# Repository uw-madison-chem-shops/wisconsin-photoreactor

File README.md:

# Wisconsin Photoreactor Platform (WPP)

An open source photoreactor platform. 3D printed enclosure, commercially available components, and a little bit of custom circuitry.

The WPP has been published in Organic Letters.
Please read our article to learn more about the motivation behind the WPP and to see examples of photochemistry being driven using this reactor.

>[Versatile Open-Source Photoreactor Architecture for Photocatalysis Across the Visible Spectrum](https://doi.org/10.1021/acs.orglett.1c01910); Philip P. Lampkin, Blaise J. Thompson, and Samuel H. Gellman; Org. Lett. 2021, 23, 13, 5277–5281

## Repository

This is an open source hardware project licensed under the CERN Open Hardware License Version 2 - Permissive.
Please see the LICENSE file for the complete license.

This repository is being mirrored to several version control systems in an attempt to ensure maximum availability.

| name             | url                                                                             |
| ---------------- | ------------------------------------------------------------------------------- |
| blaise           | https://git.blaise.zone/uw-madison-chem-shops/wisconsin-photoreactor.git/about/ | 
| Codeburg         | https://codeberg.org/uw-madison-chem-shops/wisconsin-photoreactor               |
| GitHub (primary) | https://github.com/uw-madison-chem-shops/wisconsin-photoreactor                 |
| GitLab           | https://gitlab.com/uw-madison-chem-shops/wisconsin-photoreactor                 |

## Safety

The Wisconsin Photoreactor Platform is for use by trained chemists.

WPP apparatuses utilize high-intensity light emitting diodes (LED) that can cause eye damage if proper safety precautions are not observed. 
A light-blocking shield should be utilized whenever operating a WPP apparatus.
Care must be taken to ensure the light-blocking shield employed adequately blocks light emitted by a WPP photon source from directly reaching a user.
Use of light-filtering safety glasses alongside a light-blocking shield can provide additional protection.

## Fabrication and Operation Instructions

This repository contains detailed instructions for fabrication, operation and documentation of WPP devices.
Please see [wpp-fabrication-operation.pdf](./fabrication-and-operation-instructions/wpp-fabrication-operation.pdf)

A video guide covering part sourcing, 3D-printing, electronics manufacturing, assembly and use of Wisconsin photoreactors is available on [youtube](http://www.youtube.com/watch?v=fkLr17i4FgE)

## Enclosure

The WPP is designed around a mechanically robust and simple 3D printed enclosure.

Every WPP device has the same base, see directory `photoreactor-base`.
WPP reaction modules are meant to be switched based on the reaction vessel used.
See directory `photoreactor-reaction-modules` for our growing collection of reaction modules for common vessel types.
For safe WPP device operation, a light blocking shield is recommended. 
See directory `photoreactor-light-shield`, for a 3D-printable light-blocking cover for WPP devices.

## Electronics

The WPP incorporates small custom circuit boards providing control over reaction conditions.
Please see the fabrication instructions for more detailed information.

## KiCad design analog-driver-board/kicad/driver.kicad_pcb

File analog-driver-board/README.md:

# Analog Driver Board

A simple photoreactor driver board providing control over light intensity. This control is achieved through adjustment of the board-mounted potentiometer. No software is required, and multiple WPP reactors fitted with this board can be connected in series to a single power source. However, fan speed isn’t adjustable and is maintained at maximum.

Relative light intensity can be determined using the analog driver board test points and a multimeter. See operation instructions for more information.

The analog driver board is the recommended driver solution for a typical user.

## PCB

This PCB was designed using KiCAD version 5.
Refer to `driver.pdf` for schematic.
PCB images generated with [tracespace](https://github.com/tracespace/tracespace) follow.

## Bill of Materials

| reference      | value         | manufacturer | part number       | price | vendors |
| :------------- | :------------ | :----------- | :---------------- | :---- | :------ |
| C2             | 10u           | Yageo        | CC1206KKX7R8BB106 | $0.25 | [DigiKey](https://www.digikey.com/en/products/detail/yageo/CC1206KKX7R8BB106/5195365?s=N4IgTCBcDaIMJwIxgAwDYDSGAaB2ASgBwBCxi6IAugL5A) [Mouser](https://www.mouser.com/ProductDetail/Yageo/CC1206KKX7R8BB106/?qs=%2Fha2pyFadujG%252BB25mNGWlTAfaj3wXYmzjlPMfFLRNq4azOfH13S4tw%3D%3D) |
| D1             | (red)         | Lite-On      | LTST-C230KRKT     | $0.25 | [DigiKey](https://www.digikey.com/en/products/detail/lite-on-inc/LTST-C230KRKT/386857?s=N4IgTCBcDaIDIBUDKCC0BhMBmADAaQCU8EQBdAXyA) [Mouser](https://www.mouser.com/ProductDetail/Lite-On/LTST-C230KRKT/?qs=%2Fha2pyFadujtt9TjjkxDnLsTSvKz5QHldTfy80PY7mPtEP7ka44l7w%3D%3D) |
| J3, J4         | Barrel Jack   | CUI          | PJ-002A           | $1.50 | [DigiKey](https://www.digikey.com/en/products/detail/cui-devices/PJ-002A/96962) [Mouser](https://www.mouser.com/ProductDetail/CUI-Devices/PJ-002A/?qs=WyjlAZoYn51CKfAix9Mngw%3D%3D) |
| J5             | fan connector | Sullins      | PREC040SAAN-RC    | $0.50 | [DigiKey](https://www.digikey.com/en/products/detail/sullins-connector-solutions/PREC040SAAN-RC/2774814) |
| J7             | LED connector | Molex        | 0901471102        | $0.75 | [DigiKey](https://www.digikey.com/en/products/detail/molex/0901471102/3303846) |
| R1             | 6.8k          | Yageo        | RC1206FR-076K8L   | $0.10 | [DigiKey](https://www.digikey.com/en/products/detail/yageo/RC1206FR-076K8L/729028) |
| R2             | 100           | Yageo        | RC1206FR-07100RL  | $0.10 | [DigiKey](https://www.digikey.com/en/products/detail/yageo/RC1206FR-07100RL/728491?s=N4IgTCBcDaIAQCUDCBGMAGAbAMQQWnQHYV10EAZEAXQF8g) |
| R5             | 1k            | Yageo        | RC1206FR-071KL    | $0.10 | [DigiKey](https://www.digikey.com/en/products/detail/yageo/RC1206FR-071KL/728387?s=N4IgTCBcDaIEoGECMYAMA2AYnAtKg7EgNIAyIAugL5A) |
| RV1            | 2.2k          | Bourns       | 3362P-1-202TLF    | $3.00 | [DigiKey](https://www.digikey.com/en/products/detail/bourns-inc/3362P-1-202TLF/1232538?s=N4IgTCBcDaIMxwGxgAoFoCMawAYwBUAZAMRAF0BfIA) [Newark](https://www.newark.com/bourns/3362p-1-202tlf/trimmer-potentiometer-2kohm-10/dp/33M2835) |
| TP1            | (yellow)      | Keystone     | 5014              | $0.50 | [DigiKey](https://www.digikey.com/en/products/detail/keystone-electronics/5014/255336) |
| TP2            | (red)         | Keystone     | 5010              | $0.50 | [DigiKey](https://www.digikey.com/en/products/detail/keystone-electronics/5010/255332) |
| TP3            | (black)       | Keystone     | 5011              | $0.50 | [DigiKey](https://www.digikey.com/en/products/detail/keystone-electronics/5011/255333) |        |
| U2             | LED driver    | Mean Well    | LDD-1000L (pin)  | $6.00 | [DigiKey](https://www.digikey.com/en/products/detail/mean-well-usa-inc/LDD-1000L/7704722) [Allied](https://www.alliedelec.com/product/mean-well/ldd-1000l/70345765/) [Mouser](https://www.mouser.com/ProductDetail/MEAN-WELL/LDD-1000L?qs=JK6Bpmia%2FmvDNI%252Ba1vDDrA%3D%3D) [Newark](https://www.newark.com/mean-well/ldd-1000l/dc-dc-converter-analog-pwm-30w/dp/14AJ2201) [LEDSupply](https://www.ledsupply.com/led-drivers/mean-well-ldd-l-series-cc-step-down-mode)|

All prices are extended estimates in USD.
In general, these are overestimates, so this should be an upper-estimate on cost.
Many of these components can be substituted, so take the above as suggestions.
Boards themselves can be printed for approximately $5 each.

## Changelog

### Unprinted

### Revision C

#### Changed
- Removed wisconsin crest logo

#### Revision B

#### Fixed
- Fixedsign of LED terminals on silkscreen
- Voltage divider adjusted: R1 to 6.8k R2 to 100 ohm
- Adjusted voltage divider silkscreen

### Revision A

#### Added
- Initial design

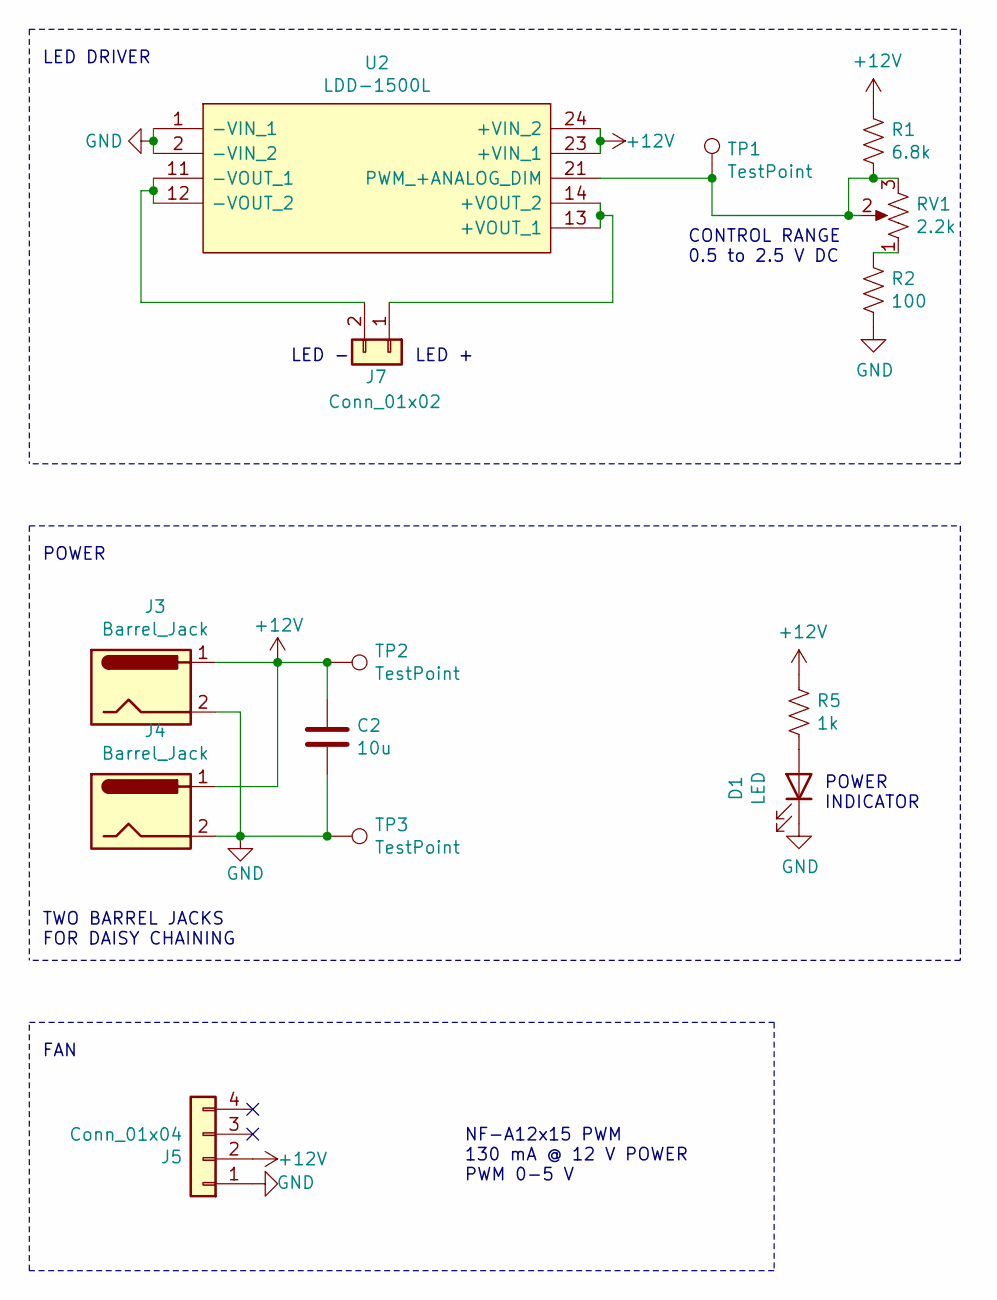
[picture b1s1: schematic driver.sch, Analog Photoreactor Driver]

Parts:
C2: 10u; C_1206_3216Metric_Pad1.33x1.80mm_HandSolder
D1: LED; LED_1206_3216Metric
J3, J4: Barrel_Jack; BarrelJack_Horizontal
J5: Conn_01x04; PinHeader_1x04_P2.54mm_Vertical
J7: Conn_01x02; PinSocket_1x02_P2.54mm_Vertical
R1: 6.8k; R_1206_3216Metric_Pad1.30x1.75mm_HandSolder
R2: 100; R_1206_3216Metric_Pad1.30x1.75mm_HandSolder
R5: 1k; R_1206_3216Metric_Pad1.30x1.75mm_HandSolder
RV1: 2.2k; TRIM_3362P-1-202TLF
TP1, TP2, TP3: TestPoint; TestPoint_THTPad_D3.0mm_Drill1.5mm
U2: LDD-1500L; LDD1500L; Manufacturer_Part_Number LDD-1500L; Mouser Part Number 709-LDD-1500L

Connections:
+12V: C2.2, J3.1, J4.1, J5.2, R1.1, R5.1, TP2.1, U2.23 (+VIN_1), U2.24 (+VIN_2)
GND: C2.1, D1.1 (K), J3.2, J4.2, J5.1, R2.2, TP3.1, U2.1 (-VIN_1), U2.2 (-VIN_2)
unnamed: D1.2 (A), R5.2
unnamed: J7.1, U2.13 (+VOUT_1), U2.14 (+VOUT_2)
unnamed: J7.2, U2.11 (-VOUT_1), U2.12 (-VOUT_2)
unnamed: R1.2, RV1.2, RV1.3, TP1.1, U2.21 (PWM_+ANALOG_DIM)
unnamed: R2.1, RV1.1

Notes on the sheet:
LED -
LED +
LED DRIVER
NF-A12x15 PWM 130 mA @ 12 V POWER PWM 0-5 V
FAN
TWO BARREL JACKS FOR DAISY CHAINING
POWER
POWER INDICATOR
CONTROL RANGE 0.5 to 2.5 V DC

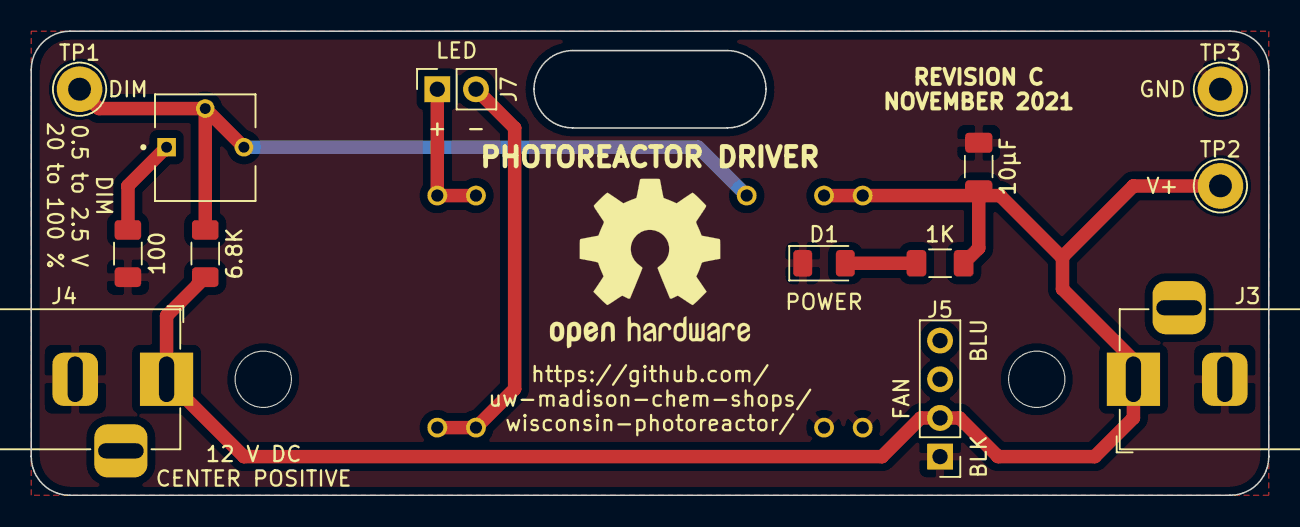
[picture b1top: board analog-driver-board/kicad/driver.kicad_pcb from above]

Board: 2 copper layers, 81.3 x 30.5 mm, 14 parts (1 on the bottom side), 7 nets.

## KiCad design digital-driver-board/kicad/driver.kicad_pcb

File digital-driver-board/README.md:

# digital-driver

A photoreactor driver board designed to be controlled digitally over I2C. For fabrication instructions, please see the fabrication and operation guide.

The digital driver is recommended for users who are experienced with electronics and interested in automating WPP devices.

## PCB

This PCB was designed using KiCAD version 5.
Refer to `driver.pdf` for schematic.
PCB images generated with [tracespace](https://github.com/tracespace/tracespace) follow.

Bill of Materials

| reference      | value         | manufacturer | part number          | price | vendors |
| :------------- | :------------ | :----------- | :------------------- | :---- | :------ |
|                | dip socket    | Mill-Max     | 110-93-308-61-001000 | $1.00 | [DigiKey](https://www.digikey.com/en/products/detail/mill-max-manufacturing-corp/110-93-308-61-001000/7734612) |
| C2             | 10u           | Yageo        | CC1206KKX7R8BB106    | $0.25 | [DigiKey](https://www.digikey.com/en/products/detail/yageo/CC1206KKX7R8BB106/5195365?s=N4IgTCBcDaIMJwIxgAwDYDSGAaB2ASgBwBCxi6IAugL5A) [Mouser](https://www.mouser.com/ProductDetail/Yageo/CC1206KKX7R8BB106/?qs=%2Fha2pyFadujG%252BB25mNGWlTAfaj3wXYmzjlPMfFLRNq4azOfH13S4tw%3D%3D) |
| C3             | 22u           | Yageo        | CC1206MKX7R7BB226    | $0.75 | [DigiKey](https://www.digikey.com/en/products/detail/yageo/cc1206mkx7r7bb226/7071713) |
| D1             | (red)         | Lite-On      | LTST-C230KRKT        | $0.25 | [DigiKey](https://www.digikey.com/en/products/detail/lite-on-inc/LTST-C230KRKT/386857?s=N4IgTCBcDaIDIBUDKCC0BhMBmADAaQCU8EQBdAXyA) [Mouser](https://www.mouser.com/ProductDetail/Lite-On/LTST-C230KRKT/?qs=%2Fha2pyFadujtt9TjjkxDnLsTSvKz5QHldTfy80PY7mPtEP7ka44l7w%3D%3D) |
| D2             | (blue)        | Lite-On      | LTST-C150TBKT        | $0.50 | [DigiKey](https://www.digikey.com/en/products/detail/lite-on-inc/LTST-C150TBKT/388526?s=N4IgTCBcDaIDIBUDKCC0BhAjAVgAwICEBpBEAXQF8g) |
| J1, J2         | i2c connector | JST          | S4B-PH-K-S(LF)(SN)   | $0.50 | [DigiKey](https://www.digikey.com/en/products/detail/jst-sales-america-inc/S4B-PH-K-S-LF-SN/926628) [Newark](https://www.newark.com/jst-japan-solderless-terminals/s4b-ph-k-s-lf-sn/connector-header-2mm-4-position/dp/38K8074) |
| J3, J4         | power input   | CUI          | PJ-002A              | $1.50 | [DigiKey](https://www.digikey.com/en/products/detail/cui-devices/PJ-002A/96962) [Mouser](https://www.mouser.com/ProductDetail/CUI-Devices/PJ-002A/?qs=WyjlAZoYn51CKfAix9Mngw%3D%3D) |
| J5             | fan connector | Sullins      | PREC040SAAN-RC       | $0.50 | [DigiKey](https://www.digikey.com/en/products/detail/sullins-connector-solutions/PREC040SAAN-RC/2774814) |
| J7             | LED connector | Molex        | 0901471102           | $0.75 | [DigiKey](https://www.digikey.com/en/products/detail/molex/0901471102/3303846) |
| PS1            | regulator     | CUI          | VXO7805-500-M-TR     | $3.00 | [DigiKey](https://www.digikey.com/en/products/detail/cui-inc/VXO7805-500-M-TR/11569188) [Newark](https://www.newark.com/cui/vxo7805-500-m-tr/non-isolated-dc-switching-regulator/dp/13AJ1536) |
| R1, R4, R6, R7 | 4.7k          | Yageo        | RC1206DR-074K7L      | $0.10 | [DigiKey](https://www.digikey.com/en/products/detail/yageo/rc1206dr-074k7l/5919134) |
| R2, R5         | 470           | Yageo        | RC1206FR-07470RL     | $0.10 | [DigiKey](https://www.digikey.com/en/products/detail/yageo/RC1206FR-07470RL/728934) |
| R3             | 10k           | Yageo        | RC1206FR-0710KL      | $0.10 | [DigiKey](https://www.digikey.com/en/products/detail/yageo/RC1206FR-0710KL/728483)  |
| U1             | microcontrol. | Microchip    | ATTINY85-20PU        | $1.50 | [DigiKey](https://www.digikey.com/en/products/detail/microchip-technology/attiny85-20pu/735469) [Newark](https://www.newark.com/microchip/attiny85-20pu/microcontroller-mcu-8-bit-attiny/dp/68T3808) |
| U2             | LED driver    | Mean Well    | LDD-1000L            | $6.00 | [DigiKey](https://www.digikey.com/en/products/detail/mean-well-usa-inc/LDD-1000L/7704722) [Allied](https://www.alliedelec.com/product/mean-well/ldd-1000l/70345765/) [Mouser](https://www.mouser.com/ProductDetail/MEAN-WELL/LDD-1000L?qs=JK6Bpmia%2FmvDNI%252Ba1vDDrA%3D%3D) [Newark](https://www.newark.com/mean-well/ldd-1000l/dc-dc-converter-analog-pwm-30w/dp/14AJ2201) [LEDSupply](https://www.ledsupply.com/led-drivers/mean-well-ldd-l-series-cc-step-down-mode)|

## I2C Interface

`<byte FAN SPEED>` `<byte LED INTENSITY>`

## Firmware

Find in "firmware" folder.

Use Arduino IDE.

We programmed the ATtiny85 using the sparkfun Tiny AVR Programmer: [PGM-11801](https://www.sparkfun.com/products/11801).

## Changelog

### Unprinted

#### Changed
- removed wisconsin crest logo

### Revision B

#### Fixed
- silk screen polarity markings for LED
- backwards I2C connectors

### Revision A

#### Added
- initial design

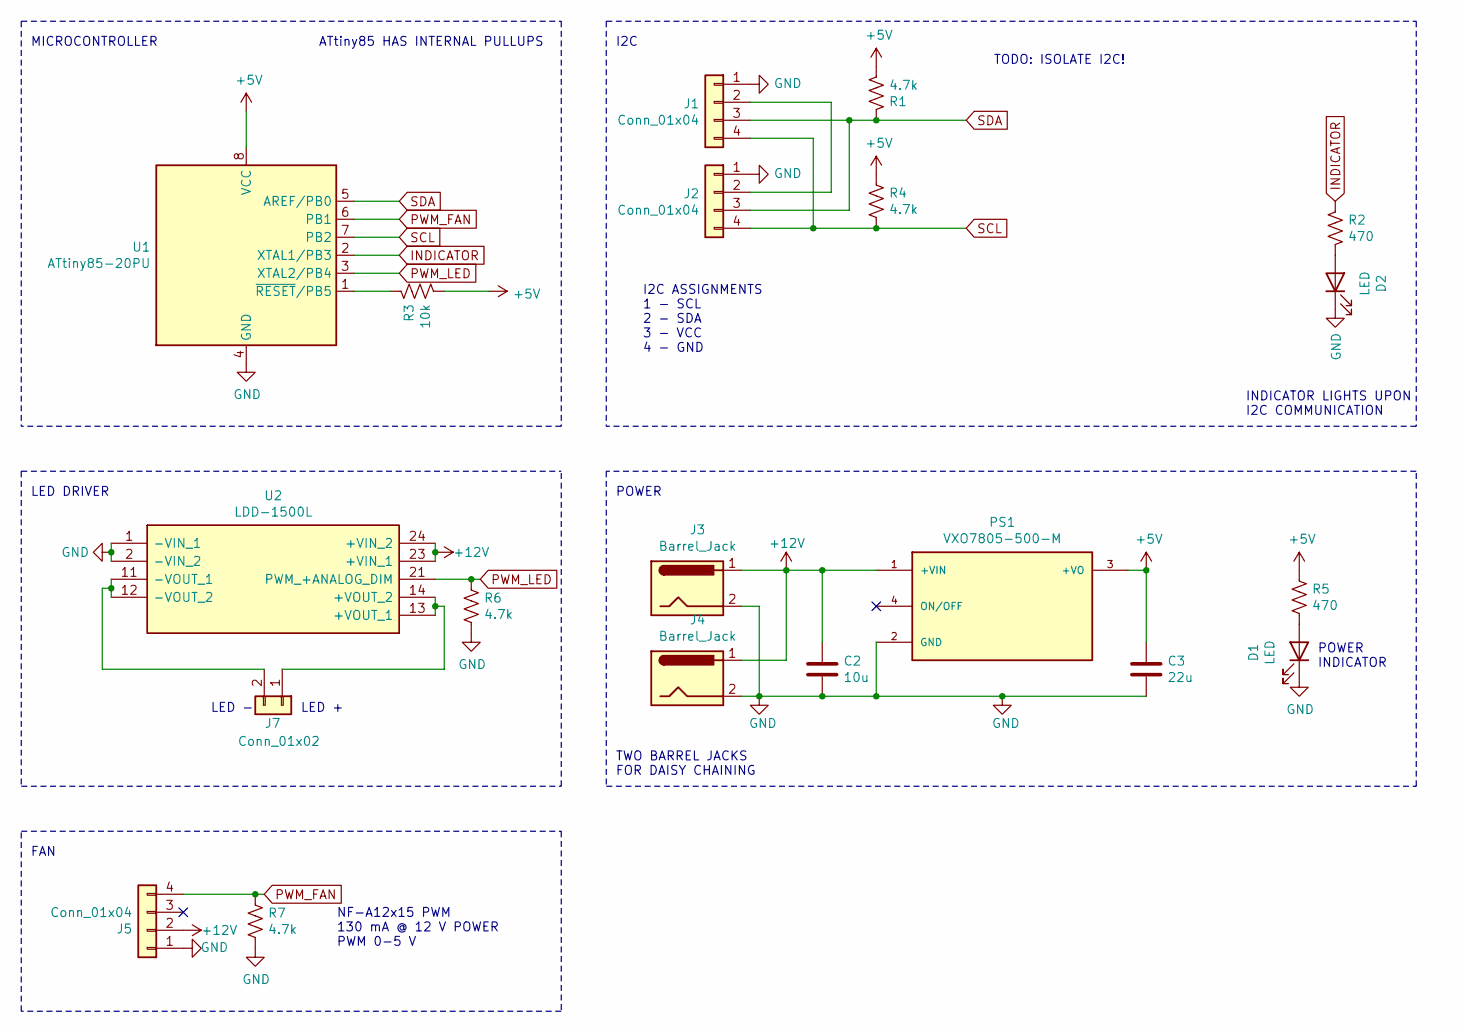
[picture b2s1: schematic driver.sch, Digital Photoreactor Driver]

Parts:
C2: 10u; C_1206_3216Metric_Pad1.33x1.80mm_HandSolder
C3: 22u; C_1206_3216Metric_Pad1.33x1.80mm_HandSolder
D1, D2: LED; LED_1206_3216Metric
J1, J2: Conn_01x04; JST_PH_S4B-PH-K_1x04_P2.00mm_Horizontal
J3, J4: Barrel_Jack; BarrelJack_Horizontal
J5: Conn_01x04; PinHeader_1x04_P2.54mm_Vertical
J7: Conn_01x02; PinSocket_1x02_P2.54mm_Vertical
PS1: VXO7805-500-M; CONV_VXO7805-500-M
R1, R4, R6, R7: 4.7k; R_1206_3216Metric_Pad1.30x1.75mm_HandSolder
R2, R5: 470; R_1206_3216Metric_Pad1.30x1.75mm_HandSolder
R3: 10k; R_1206_3216Metric_Pad1.30x1.75mm_HandSolder
U1: ATtiny85-20PU; DIP-8_W7.62mm_Socket
U2: LDD-1500L; LDD1500L; Manufacturer_Part_Number LDD-1500L; Mouser Part Number 709-LDD-1500L

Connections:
+5V: C3.1, PS1.3 (+VO), R1.2, R3.1, R4.1, R5.1, U1.8 (VCC)
+12V: C2.2, J3.1, J4.1, J5.2, PS1.1 (+VIN), U2.23 (+VIN_1), U2.24 (+VIN_2)
GND: C2.1, C3.2, D1.1 (K), D2.1 (K), J1.1, J2.1, J3.2, J4.2, J5.1, PS1.2 (GND), R6.2, R7.2, U1.4 (GND), U2.1 (-VIN_1), U2.2 (-VIN_2)
INDICATOR: R2.1, U1.2 (XTAL1/PB3)
unnamed: D1.2 (A), R5.2
unnamed: D2.2 (A), R2.2
unnamed: J1.2, J2.2
unnamed: J7.1, U2.13 (+VOUT_1), U2.14 (+VOUT_2)
unnamed: J7.2, U2.11 (-VOUT_1), U2.12 (-VOUT_2)
unnamed: R3.2, U1.1 (~RESET~/PB5)
PWM_FAN: J5.4, R7.1, U1.6 (PB1)
PWM_LED: R6.1, U1.3 (XTAL2/PB4), U2.21 (PWM_+ANALOG_DIM)
SCL: J1.4, J2.4, R4.2, U1.7 (PB2)
SDA: J1.3, J2.3, R1.1, U1.5 (AREF/PB0)

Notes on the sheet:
POWER
TWO BARREL JACKS FOR DAISY CHAINING
MICROCONTROLLER
ATtiny85 HAS INTERNAL PULLUPS
I2C ASSIGNMENTS 1 - SCL 2 - SDA 3 - VCC 4 - GND
POWER INDICATOR
LED -
LED +
LED DRIVER
FAN
INDICATOR LIGHTS UPON I2C COMMUNICATION
I2C
NF-A12x15 PWM 130 mA @ 12 V POWER PWM 0-5 V
TODO: ISOLATE I2C!

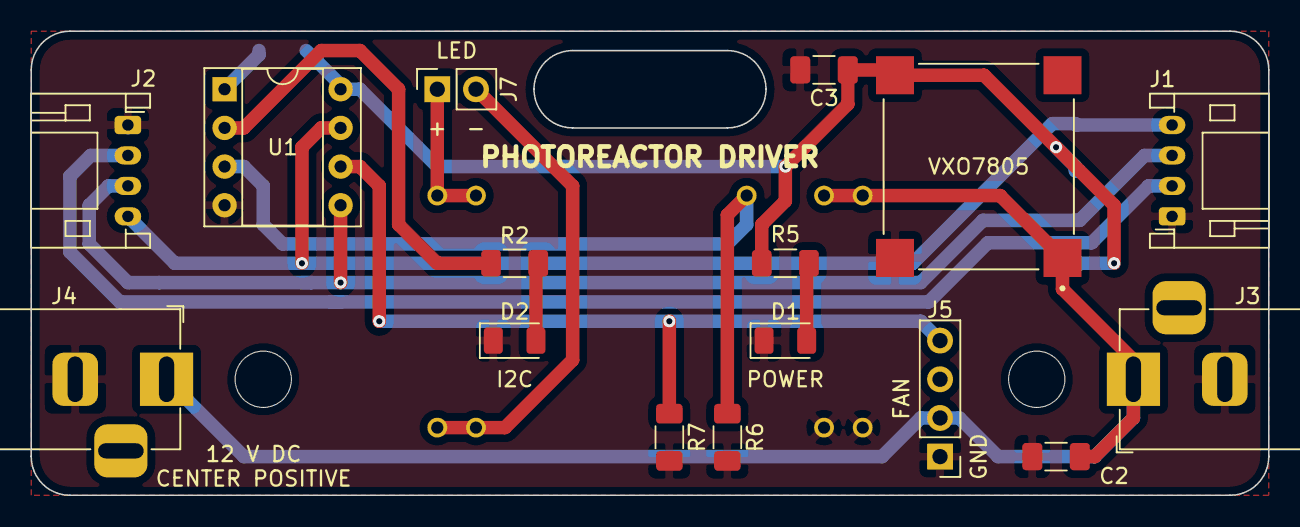
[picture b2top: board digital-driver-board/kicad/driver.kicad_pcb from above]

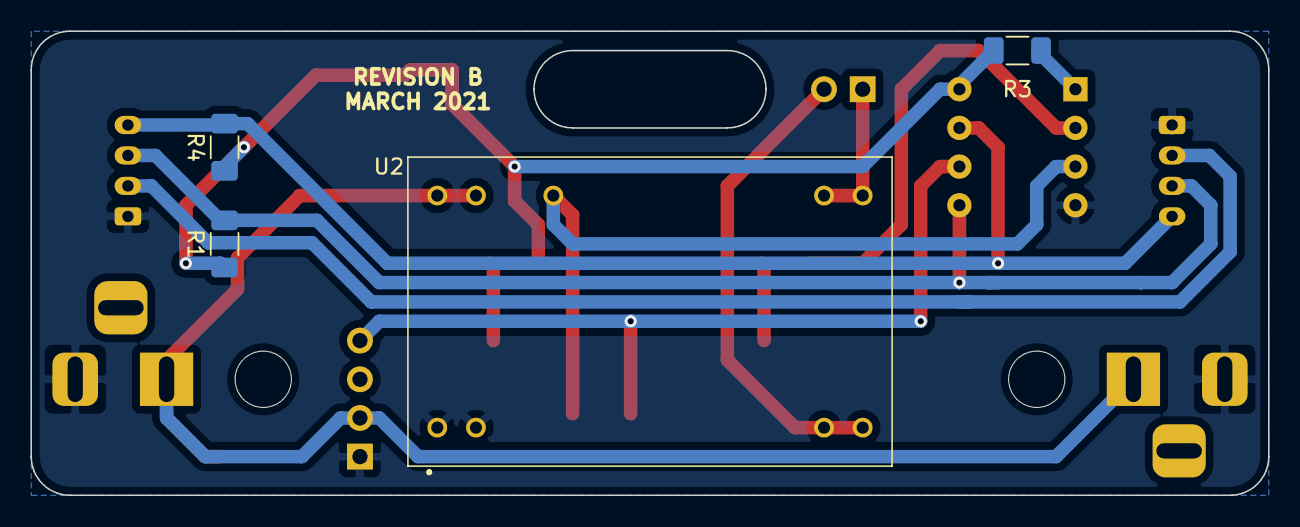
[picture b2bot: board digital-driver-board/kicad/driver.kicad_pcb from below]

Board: 2 copper layers, 81.3 x 30.5 mm, 20 parts (4 on the bottom side), 14 nets.

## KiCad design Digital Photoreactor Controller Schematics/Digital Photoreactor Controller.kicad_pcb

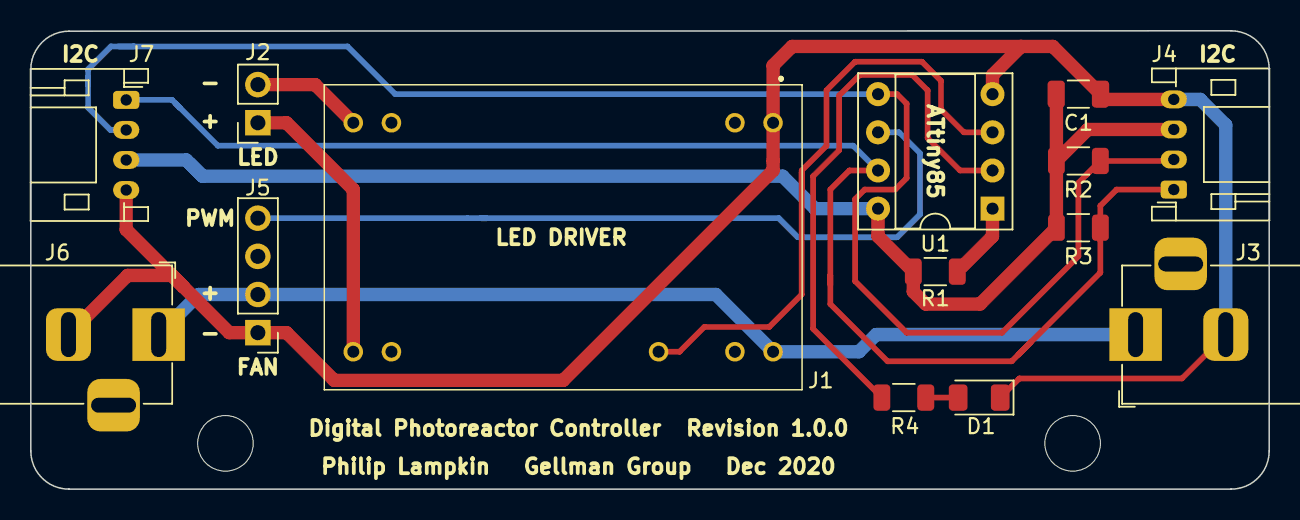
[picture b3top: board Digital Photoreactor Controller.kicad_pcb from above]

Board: 2 copper layers, 82.4 x 30.5 mm, 14 parts (0 on the bottom side), 12 nets.

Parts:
C1: 0.1uF; C_1206_3216Metric
D1: LED; LED_1206_3216Metric
J1: LDD-1500L; LDD1500L
J2: Conn_01x02; PinSocket_1x02_P2.54mm_Vertical
J3, J6: Barrel_Jack; BarrelJack_Horizontal
J4, J7: Conn_01x04; JST_PH_S4B-PH-K_1x04_P2.00mm_Horizontal
J5: Conn_01x04; PinHeader_1x04_P2.54mm_Vertical
R1: 10K; R_1206_3216Metric
R2, R3: 4.7K; R_1206_3216Metric
R4: 470; R_1206_3216Metric
U1: ATtiny85-20PU; DIP-8_W7.62mm_Socket

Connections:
+5V: C1.1, J4.3, J7.3, R1.1, R2.1, R3.1, U1.8
+12V: J1.24, J3.1, J5.2, J6.1
GND: C1.2, D1.1, J1.1, J3.2, J4.4, J5.1, J6.2, J7.4, U1.4
INDICATOR: R4.2, U1.2
unnamed: D1.2, R4.1
unnamed: J1.12, J2.2
unnamed: J1.13, J2.1
unnamed: R1.2, U1.1
PWM_FAN: J5.4, U1.6
PWM_LED: J1.21, U1.3
SCL: J4.1, J7.1, R3.2, U1.7
SDA: J4.2, J7.2, R2.2, U1.5

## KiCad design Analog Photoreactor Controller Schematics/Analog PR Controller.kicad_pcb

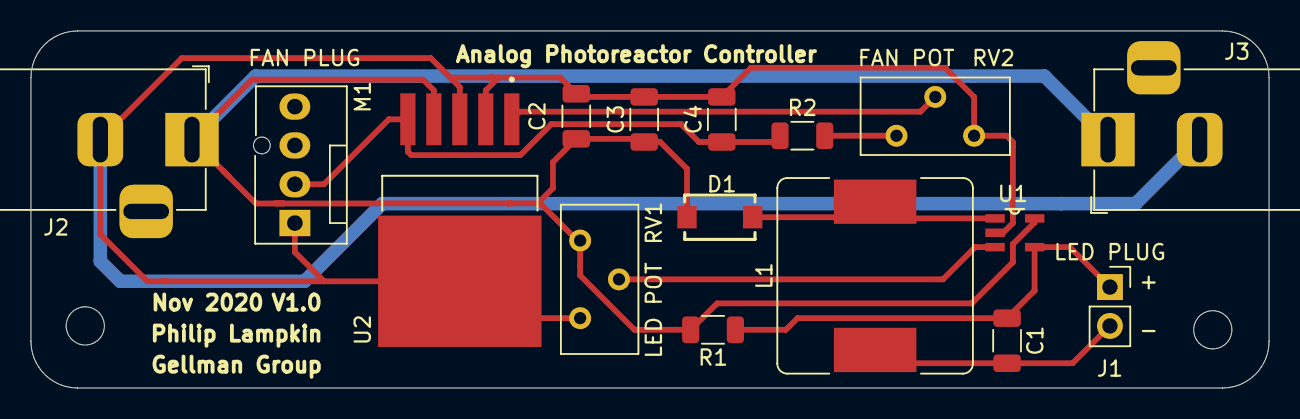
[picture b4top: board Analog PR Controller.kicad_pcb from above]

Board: 2 copper layers, 81.0 x 23.4 mm, 16 parts (0 on the bottom side), 9 nets.

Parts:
C1: 1uF; C_1206_3216Metric
C2: 2.2uF; C_1206_3216Metric
C3: 0.47uF; C_1206_3216Metric
C4: 22uF; C_1206_3216Metric
D1: MBRA140; SMA-DIODE
J1: Conn_01x02; PinSocket_1x02_P2.54mm_Vertical
J2, J3: Barrel_Jack; BarrelJack_Horizontal
L1: 33uH; L_Bourns_SRR1260
M1: Fan_4pin; FanPinHeader_1x04_P2.54mm_Vertical
R1: 0.3R; R_1206_3216Metric
R2: 8KOhm; R_1206_3216Metric
RV1: 100KOhm; Potentiometer_Bourns_3296Y_Vertical
RV2: 5kOhm1; Potentiometer_Bourns_3296Y_Vertical
U1: AL8805W5-7; SOT95P280X130-5N
U2: LM2941S; VREG_TPS79625KTTR

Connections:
+12V: C2.2, C3.1, D1.C, J2.1, J3.1, R1.2, RV1.1, U1.5, U2.4
GND: C2.1, C3.2, C4.2, J2.2, J3.2, M1.1, RV1.3, RV2.3, U1.2, U2.2, U2.3, U2.6
unnamed: C1.1, J1.1, R1.1, U1.4
unnamed: C1.2, J1.2, L1.1
unnamed: C4.1, M1.2, R2.1, U2.5
unnamed: D1.A, L1.2, U1.1
unnamed: R2.2, RV2.1
unnamed: RV1.2, U1.3
unnamed: RV2.2, U2.1

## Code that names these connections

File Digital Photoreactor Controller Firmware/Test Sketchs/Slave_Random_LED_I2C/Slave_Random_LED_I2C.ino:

////////////////////////////////////////////////////////////////////////////////////
// I2C test program for Digital Photoreactor Controller using TinyWireS library   //
//                    Run this slave program on the AtTiny85.                     //      
////////////////////////////////////////////////////////////////////////////////////
// This test program is adapted from the TinyWireS stress test program            //
// developed by Scott Hartog: https://github.com/rambo/TinyWire                   //
//                                                                                //
// The slave program receives via I2C N bytes of random data in a single          //
// receiveEvent() callback and stores that data in a global buffer.               //
// It then responds the first requestEvent() callback with the same data.         //
// The requestEvent() callback overwrites the data buffer with zeros after        //
// responding so it will only respond correctly to the first requestEvent()       //
// callback after each receiveEvent() callback. Subsequent requestEvent()         //
// will respond with 0xff for all data bytes.                                     //
//                                                                                //
//                                                                                //
// SETUP:                                                                         //
// AtTiny85 Pin 2 = PB3 = Blink LED                                               //
// Attiny85 Pin 3 (PB4) = LED PWM                                                 //
// AtTiny85 Pin 5 (PB0/SDA) = I2C SDA                                             //
//     connect to SDA on master with external pull-up (~4.7K)                     //
// AtTinyPin 6 (PB1) = Fan PWM                                                    //
// AtTiny Pin 7 (PB0/SCL) = I2C SCL                                               //
//     connect to SCL on master with external pull-up (~4.7K)                     //
// AtTiny Pin 1 (PB5/!RST)                                                        //
//     connect to reset on master (or just pull-up)                               //
//                                                                                //
////////////////////////////////////////////////////////////////////////////////////

#include "TinyWireS.h"                  // wrapper class for I2C slave routines

#define I2C_SLAVE_ADDR  0x26            // I2C slave address (38, 0x26), 

uint8_t master_data[16];               // global buffer to store data sent from the master.
uint8_t master_bytes;                  // global variable to number of bytes sent from the master.

const int LEDPin = 4;                  //Arduino pin 4, pin 3 on AtTiny85 pinout
const int FanPin = 1;                  //Arduino pin 1, pin 6 on AtTiny85 pinout
const int BlinkPin = 3;                //Arduino pin 3, pin 2 on AtTiny85 pinout

// Gets called when the ATtiny85 receives an I2C write slave request
void receiveEvent(uint8_t num_bytes)
{
  uint8_t i;
  
  // save the number of bytes sent from the master
  master_bytes = num_bytes;

  // store the data from the master into the data buffer
  for (i = 0; i < master_bytes; i++)
    master_data[i] = TinyWireS.receive();

  // set LED and Fan PWM duty to random byte values recieved from the master
  analogWrite(FanPin, master_data[0]);
  analogWrite(LEDPin, master_data[1]);

  // blink LED whenever data is successfuly recieved
  digitalWrite(BlinkPin, HIGH);
  delay(10);
  digitalWrite(BlinkPin, LOW);
  delay(10);

}

// Gets called when the ATtiny receives an i2c read slave request
void requestEvent()
{
  uint8_t i;
  
  // send the data buffer back to the master
  for (i = 0; i < master_bytes; i++)
    TinyWireS.send(master_data[i]);

  // corrupt the byte values in the data buffer
  // so that subsequent call won't match
  for (i = 0; i < master_bytes; i++)
    master_data[i] += 0x5a;

  // corrupt length of the request, but dont' make it zero
  
  // if the usiTwiSlave.c is working fine, then this number is completely irrelevant
  // because the requestEvent() callback will not be called again until
  // after the next receiveEvent() callback, so the master_data and
  // master_bytes variables will be set by that call.

  // If the usiTwiSlave.c has the issue of calling the requestFrom() callback
  // for each byte sent, the buffer will accumulate by this amount *for each byte
  // in the original request*.
  // 
  // Making it zero will obscure the 1-byte send issue in the usiTwiSlave.c
  // that is being tested.
  // Making it small will allow a few requests to succeed before the tx buffer
  // overflows and the usiTwiSlave.c hangs on the "while ( tmphead == txTail );"
  // line
  master_bytes = 2; 
}

void setup()
{
  // initialize the TinyWireS and usiTwiSlave libraries
  TinyWireS.begin(I2C_SLAVE_ADDR);      // init I2C Slave mode

  // register the onReceive() callback function
  TinyWireS.onReceive(receiveEvent);
  
  // register the onRequest() callback function
  TinyWireS.onRequest(requestEvent);

  pinMode(LEDPin, OUTPUT);   // set pin for LED PWM
  pinMode(FanPin, OUTPUT);   // set pin for Fan PWM
  pinMode(BlinkPin, OUTPUT); // set pin to blink LED
  
  TCCR0B = TCCR0B & 0b11111000 | 0b001; // sets internal timer of AtTiny85 to 31250 Hz for fast PWM for controlling fan speed
}

void loop()
{
  // this needs to be here 
  /////////////Does this really need to be here?????
  //TinyWireS_stop_check();
  // otherwise empty loop
}

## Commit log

2020-12-29 updated PCB w/ LED
2020-12-30 Commented and added blink LED function on receive data
2020-12-30 Commented and cleaned up code
2020-12-30 Wrote PR controller sketches for slave and master
2020-12-30 markdown readme
2020-12-30 Updated PCB routing
2020-12-30 Updated drill marks and edgecuts to be more uniform
2020-12-30 Added optimized lightsource bases in open and closed configuration
2021-01-06 Removed version numbers, removed open base, added final optimized closed base design
2021-01-19 restructure repository
2021-01-19 cleanup analog photoreactor
2021-01-19 cleanup documentation directory
2021-01-19 cleanup digital driver
2021-01-21 updated base to use heat insets, have compatability with zip tie anchors and better mounts for driver board
2021-01-25 digital driver prototype
2021-01-25 digital-driver readme
2021-01-25 digital-driver table newline
2021-01-25 tap-heatsink
2021-01-27 digital driver 1.0.0
2021-01-29 analog driver 1.0.0
2021-01-29 analog readme
2021-02-11 updated base designs
2021-03-05 analog-driver revision B
2021-03-05 parts list
2021-03-05 rearrange repository
2021-03-05 delete
2021-03-06 added enclosures for new vessel types, added WPR logo to base and cleaned up file names
2021-03-06 added LED emission spectra
2021-03-06 added README
2021-03-06 digital driver revision B
2021-03-06 emission spectra pictures
2021-03-06 rename
2021-03-06 duplicate removal
2021-03-12 updated amber spectrum
2021-03-25 coverart
2021-03-25 license
2021-03-25 organize analog-driver
2021-03-25 analog readme levels
2021-03-25 assembly instructions skeleton
2021-04-14 assembly skeleton
2021-04-14 new photos
2021-04-16 pcb assembly pictures
2021-04-16 led pictures
2021-04-19 first minimum viable assembly instructions
2021-04-19 populate readme
2021-04-24 added typical photon source emission spectra
2021-04-24 reworked LED emission spectra terminology
2021-04-24 updated LED terminology
2021-04-24 rename leds directory
2021-04-24 new coverart
2021-04-24 terminology update
2021-04-24 terminology updates
2021-04-24 added modules photo
2021-04-24 added base photo
2021-04-24 rough merge of content from operation instructions
2021-04-24 updated controller firmware with serial interface
2021-04-24 remove wisconsin crest logo
2021-04-25 Updated fabrication and operation guide up and including analog driver
2021-04-26 complete digital bom
2021-04-26 updated guide figures and text
2021-04-26 programming instructions
2021-04-26 added initial digital driver fabrication guide
2021-04-27 cleaned up digital driver board portion
2021-04-27 formatted documentation section
2021-04-27 polished entire guide
2021-04-27 Update README.md
    fixed spelling and updated wording.
2021-04-27 Update README.md
    updated wording and fixed spelling
2021-04-27 Update README.md
    Fixed wording and spelling
2021-04-27 Update README.md
    Fixed wording and spelling.
2021-04-27 Update README.md
    updated wording, fixed spelling.
2021-04-27 Update README.md
    Fixed wording.
2021-04-27 document fan, led connectors
2021-04-27 actually link to pdf
2021-04-27 added completed digital board figure
2021-04-27 updated guide with figure
2021-04-28 Edits from Sam
2021-04-28 Edits from Sam round 2
2021-05-18 Fixed photoreactor base naming, WPP branding and heat inset depth
2021-05-18 Updated README.md
    Added correct manufacturer part numbers
2021-05-18 updated 1mL to 2mL and item number
2021-05-18 Update README.md
    Added extra vendors for LDD-1000L driver
2021-05-18 Update README.md
    added LDD-1000L vendors
2021-05-18 updated fab guide 1mL to 2mL
2021-05-18 Update README.md
    added links to LED stars from LEDsupply
2021-05-19 fixed naming conventions
2021-05-19 removed Logos from all figures
2021-05-19 Cleaned up fabrication guide directory
2021-05-19 updated base graphic
2021-05-19 updated fab/op guide title page
2021-05-24 added light shield
2021-05-26 updated safety guide with light shield information
2021-05-26 added light shield photo to subdirectory
2021-05-26 updated operations guide title page
2021-05-26 Updated test point voltage --> LED intensity
2021-05-26 compressed light shield photo size
2021-06-16 updated fab guide grammar/spelling
2021-07-07 add citation to readme
2021-07-07 formatting
2021-08-04 remove chem repo, add codeburg
2021-08-04 blaise
2021-11-30 add url to analog driver board
2021-11-30 analog driver readme
